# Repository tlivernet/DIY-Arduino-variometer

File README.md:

DIY Arduino variometer - with BMP085 Barometric Pressure Sensor
==================

> ### 🚧 Une refonte moderne est en cours : [`vario-esp32/`](vario-esp32/)
>
> Ce projet de 2014-2017 reste utilisable, mais il ne compile que sur l'IDE Arduino 1.5-1.6.1 et ses composants (BMP085, DS1307, Nokia 5110) ne se trouvent plus.
>
> Une refonte complète sur **ESP32-S3** est engagée dans le dossier [`vario-esp32/`](vario-esp32/) : écran Sharp Memory LCD 400×240, vario compensé en accélération par filtre de Kalman, liaison BLE vers XCTrack, PCB KiCad et boîtier imprimé en 3D, pour ~42 €. Le cœur métier y est déjà porté et couvert par 70 tests, dont un test de non-régression par bug identifié dans la version ci-dessous.
>
> Le code AVR historique de cette page n'est pas modifié.

Il s'agit de la version utilisant le capteur de pression BMP085. 
Vous trouverez une version alternative de ce code supportant le MS5611 sur la branche "[MS5611](https://github.com/sinseman/DIY-Arduino-variometer/tree/MS5611)".

- [Mise à jour](#mise-à-jour)
- [Présentation](#présentation)
- [Schéma](#schéma)
- [Installation](#installation)
- [Interface et utilisation](#interface-et-utilisation)

## MISE À JOUR

**Attention !** Lors de la dernière mise à jour le schéma de connection de l'écran a été modifié pour des soucis d'optimisations du montage.

- **PIN\_SCLK** : D8 --> D4
- **PIN\_LIGHT** : D11 --> Inchangée
- **PIN\_SCE** : D7 --> Inchangée
- **PIN\_RESET** : D6 --> D8
- **PIN\_DC** : D5 --> D6
- **PIN\_SDIN** :  D4 --> D5

Bien sûr vous pouvez adapter le code suivant l'ordre des branchements de l'écran à votre disposition.

Cela est valable aussi avec l'encodeur digital pour inverser le sens de rotation en remplaçant ```
Encoder knob(3, 2);``` par ``` Encoder knob(2, 3);```

**Il faut également ré-initialiser la mémoire EEPROM en téléversant une première fois avec la variable initialisation à true puis re-téléverser avec initialisation à false (voir partie [Installation](#installation)).**

## Présentation
### Vidéo de démo

[Participer à la discussion sur le forum parapentiste.](http://www.parapentiste.info/forum/bons-plans/variometre-maison-a-base-darduino-t33538.0.html)

### Matériel et coût

Le but de ce projet est de fabriquer un variomètre à faible coût pour une utilisation en vol libre (dans mon cas la pratique du parapente).
Voici à titre indicatif le matériel utilisé et leur prix d'achat sur eBay international (prix de janvier 2014) :

- Arduino nano V3.0	| 5,10€
- Nokia LCD 5110 | 2€
- BMP085 Digital Barometric Pressure Sensor	| 2,90€
- Digital Push Button Switch Rotary Encoder	| 4,20€
- Mini USB Battery Charging Board 5V | 0,90€
- Buzzer 8 ohm | 0,20€
- DC-DC Converter Step Up 1-5V 500mA | 1,15€
- 3,7V 600mAh LiPo Battery | 3,25€
- RTC Module for Arduino | 1,55€
- 3x 10k Ohm resistor + 1x 120 Ohm resistor | 0,10€
- Right Angle Mini Slide Switch | 0,10€	
- Cables | 3€
- Plastic Electronics Project Box Enclosure DIY 27x60x100mm | 2,40€

**TOTAL	| 26,85 €**

## Schéma

## Installation

Une fois votre montage terminé il faut compiler et téléverser le code sur votre Arduino. Pour cela il vous faudra utiliser l'IDE Arduino.

**Il faut utiliser [une version de l'IDE Arduino >= 1.5 et <= 1.6.1](https://www.arduino.cc/en/Main/OldSoftwareReleases), sinon des erreurs de compilation apparaissent !**

Tout d'abord vous devez installer les librairies fournies avec le projet. Copiez le contenu du dossier librairies dans le dossier librairies de votre installation (par exemple C:\Users\Toto\Documents\Arduino\libraries)

Ensuite éditez avec l'IDE Arduino le fichier Variometer/Variometer.ino et cliquez sur le bouton "Vérifier" en haut du logiciel. Après un certain temps le message "Compilation terminée" devrait apparaitre. Si vous avez des erreurs vérifiez que les librairies sont bien installées (cf plus haut).

Une fois la compilation OK il faut téléverser le programme sur l'Arduino à l'aide d'un câble USB par exemple et en cliquant sur le bouton "Téléverser" de l'IDE. **Mais avant cela lisez ce qui suit !**

**Lors du premier téléversement du programme sur l'Arduino il est important de mettre dans le code la variable  initialisation à true.
Celle-ci permet d'initisaliser correctement la mémoire Eeprom (stockant les statistiques et les options).**

```
bool initialisation = true; 
```

**Une fois le premier allumage fait il faut donc re-téléverser le code avec cette fois-ci initialisation à false. Si cela n’est pas fait la mémoire Eeprom sera effacée à chaque allumage !**

```
bool initialisation = false; 
```

## Interface et utilisation

Ce variomètre utilise un minimum de commande pour naviguer dans le menu et interagir avec l'interface. Nous utilisons un encodeur digital permettant trois actions: Gauche - Droite - Valider.

L'écran est celui d'un Nokia 5110, donc plutôt petit comparé aux variomètres du commerce, mais les informations essentielles y sont affichées. Ce variomètre produit des "bips" qui sont aussi bien émis lors de la navigation dans le menu que lors de l'utilisation de l'interface vario. 
Le volume est bien entendu paramétrable ainsi que la sensibilité de déclenchement en monté et en descente.

En plus de fournir des informations en temps réel, un système de détection automatique du début et de fin de vol permet d'obtenir des statistiques intéressantes.

### Menu

- Vario
- Stats
	- Retour
	- Statistiques
	- Reset
- Options
	- Retour
	- Tare
	- QNH
	- Alti
	- Montee
	- Desc
	- Light
	- Contra
	- Date

### Vario

Affichage dynamique des éléments suivants :

- Altitude (m)
- Variation d'altitude (m/s) avec jauge dynamique
- Temps de vol (heure : minute : seconde)
- Heure
- Température
- Batterie

Le réglage du volume est possible en tournant l'encodeur digital.
Lors d'un appui long sur le poussoir de l'encodeur, les statistiques sont réinitialisées.

### Stats

L'enregistrement des statistiques de vol se déclenche automatiquement.
Pour cela le variomètre détecte une prise ou une baisse d'altitude significative entrainant le statut "en vol".
Lorsqu'il n'y a pas de baisse ou de prise d'altitude significative pendant un certain temps, le statut "en vol" s'arrête.

A la fin du vol les statistiques sont sauvegardées et ne sont pas perdues à l'extinction du variomètre.

Ce programme peut enregistrer 8 rapports de vol. Une fois un vol terminé, la piste suivante d'enregistrement est sélectionnée. Si celle-ci n'est pas vide elle n'est pas écrasée. Il faut alors manuellement effacer la plage de stat en cours (avec un appui long sur le bouton depuis l'interface Vario) ou reset toutes les plages (Menu Stats --> Reset).

**Statistique**

Voici les informations statistiques disponibles :

- Date
	- Date et heure de début de vol.

- Chrono
	- Temps de vol enregistré, exprimé en heure : minute : seconde.

- AltMin
	- L'altitude minimum en mètre enregistré pendant le vol.

- AltMax
	- L'altitude maximum en mètre enregistré pendant le vol.

- Tx de chutte
	- Les taux de chute maximum et minimum en mètre par seconde enregistrés pendant le vol.

- Cumul
	- Altitude cumulée du vol (en mètre).

**Reset**

Remise à zéro des statistiques.

### Options

**Tare**

Initialise l'altitude zéro sur l'altitude actuelle.

**QNH**

Pression atmosphérique convertie au niveau de la mer selon les conditions de l'atmosphère standard.

**Alti**

Permet d'ajuster l'altitude.

**Montee**

Taux de montée déclenchant le bip.

**Desc**

Taux de descente déclenchant le bip.

**Light**

Intensité du rétro-éclairage (Off à 5)

**Contra**

Ajustement du contraste de l'écran.

**Date**

Réglage de la date et de l'heure de la pendule.

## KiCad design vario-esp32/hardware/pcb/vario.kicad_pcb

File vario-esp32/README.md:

# Variomètre ESP32-S3

Refonte complète du [variomètre DIY sur Arduino Nano](../README.md) de 2014-2017, pour du matériel sourçable en 2026 et une chaîne de développement qui fonctionne encore dans dix ans.

> **État : le coeur logiciel est terminé et testé — 166 tests.** Les pilotes matériel, le PCB et le boîtier arrivent aux étapes suivantes (voir [Feuille de route](#feuille-de-route)). **Rien de tout ceci n'a encore volé.**
>
> Documentation : `mkdocs serve` (ou voir `docs/`). Écrans rendus : `make render`.
>
> Le firmware **compile** pour l'ESP32-S3 (RAM 9,9 %, flash 12,2 %), mais aucun pilote n'a encore tourné sur du matériel.

## Pourquoi une refonte

Le montage d'origine fonctionne et il vole, mais :

- il ne compile que sur l'IDE Arduino 1.5-1.6.1, sorti en 2015 ;
- le BMP085 et le DS1307 ne se trouvent plus ;
- le vario a ~0,8 s de retard et ~0,3-0,4 m/s de bruit affiché, soit **plus que son propre seuil de déclenchement** à 0,3 m/s — d'où un bipeur qui bavarde à l'arrêt ;
- il n'a aucun test, et dix bugs identifiés dont deux graves (chrono qui ne s'arrête jamais, enregistrement qui cesse au bout de 8 vols).

## Ce qui est déjà là

Le coeur métier, en C++17 pur — aucune dépendance à Arduino, donc compilable et testable sur PC :

| Module | Rôle |
|---|---|
| `core/isa` | conversion pression → altitude (atmosphère standard), QNH borné |
| `core/vario_filter` | lissage pression + dérivée, coefficients indépendants de la cadence |
| `core/attitude` | estimation d'assiette 6 axes, **compensation centrifuge** |
| `core/kalman` | filtre à 3 états (altitude, vitesse, biais), garde de divergence |
| `core/audio_gate` | inhibition du son pendant la convergence au démarrage |
| `core/tone_law` | lois hauteur/durée des bips, profils « classique » et « moderne » |
| `core/tone_scheduler` | machine à états du bipeur : amorce continue, note, pause, hystérésis |
| `core/flight_fsm` | détection automatique décollage / atterrissage |
| `core/stats` | statistiques de vol (extrema, gain cumulé) |
| `core/flight_log` | journal en ajout seul, enregistrements de 64 octets + CRC16 |
| `core/config_schema` | table de schéma pilotant NVS, menu embarqué et IHM web |
| `core/lk8ex1` | trames LK8EX1 pour XCTrack / XCSoar |
| `core/buttons` | machine à états des trois boutons (anti-rebond, appui long, répétition) |
| `core/battery` | jauge de batterie 1S |
| `core/format` | mise en forme de la vitesse verticale |
| `ui/canvas` | tampon 1 bit, primitives, suivi des lignes modifiées |
| `ui/segment` | chiffres à sept segments, de taille libre |
| `ui/screens` | écrans vario, calibration, statistiques, menu |

**166 tests** répartis en 14 suites, dont un test de non-régression nommé pour chacun des dix bugs de la version AVR.

### Testé sans matériel

Deux techniques rendent l'essentiel vérifiable sur un PC :

- **trajectoires synthétiques** — accéléromètre, gyromètre et pression dérivés d'une même vérité terrain. Le jeu décisif est le virage coordonné établi : vitesse verticale vraie nulle mais facteur de charge de `g/cos φ`, situation où un vario naïf annonce une fausse montée de 1,5 m/s ;
- **images de référence** — les écrans sont rendus puis comparés octet par octet à des PBM versionnés.

## Installer l'environnement

```bash
./tools/doctor.sh          # ce qui manque, et pour quelle étape
./tools/setup-linux.sh     # installation guidée (--dry-run pour voir sans agir)
```

Pour seulement lancer les tests, trois paquets suffisent : `build-essential`, `git`, `python3`. Détail par usage dans [`docs/environnement.md`](docs/environnement.md).

## Compiler et tester

```bash
# Tests du coeur métier — c'est ce que vérifie la CI
make test

# Une seule suite
make test-test_kalman

# Rendre les écrans dans build/screens/*.png
make render

# Regénérer les images de référence (après un changement de mise en page ASSUMÉ)
make golden

# Firmware embarqué (nécessite PlatformIO)
pio run -e esp32s3
```

`make test` n'a besoin que de `g++` et `make` : Unity est inclus dans le dépôt (`test/support/unity`, licence MIT). `pio test -e native` fait la même chose via PlatformIO si tu préfères.

## Matériel visé

| Poste | Choix | Prix indicatif |
|---|---|---|
| MCU | ESP32-S3 (USB natif, BLE 5, 2 cœurs) | 5 € |
| Baromètre | MS5611 (derrière une interface, un BMP390 doit pouvoir le remplacer) | 4 € |
| IMU | 6 axes, pour le vario compensé en accélération | 2 € |
| Écran | Sharp Memory LCD LS027B7DH01, 400×240 | 18 € |
| Audio | piezo large bande + tampon 5 V | 1 € |
| Commande | 3 boutons étanches (gants) | 1 € |
| Horloge | DS3231SN + pile de sauvegarde | 1,5 € |
| Énergie | LiPo 1S 1500 mAh + charge USB-C | 6 € |
| Divers + PCB + PETG | | 5 € |
| **Total** | | **≈ 42 €** |

À comparer aux 26,85 € de la version 2014 (avec un écran à 2 €) et aux 250-400 € d'un vario du commerce.

Le Sharp Memory LCD a été retenu plutôt qu'un e-paper : même lisibilité en plein soleil et consommation quasi nulle à l'affichage figé, mais rafraîchissement rapide et **fonctionnement par grand froid** — un e-paper standard ralentit fortement sous 0 °C, ce qu'on rencontre couramment à 3000 m.

## Apports par rapport à la version AVR

- **Vario compensé en accélération** : fusion baro + accéléromètre par filtre de Kalman. La latence ne vient plus du filtre mais de l'intégration directe de l'accélération — d'où ~0,2 s au lieu de ~0,8 s, *et* un bruit divisé par 4 à 8 en même temps.
- **Seuil de montée utilisable à 0,2 m/s**, puisque le plancher de bruit descend sous 0,1 m/s.
- **Configuration au navigateur** par portail Wi-Fi, au lieu d'une molette et d'un écran de 84×48.
- **BLE vers XCTrack / XCSoar** (trames LK8EX1) : le vario sert aussi de capteur au téléphone.
- **Journal de vol append-only** en LittleFS, avec CRC et récupération après coupure — un vol interrompu par une batterie vide n'est plus perdu.
- **Silence au repos**, garanti par un test.

## Les dix bugs de 2017, et leur test

Chaque ligne correspond à un test de non-régression nommé dans `test/`.

| # | Bug | Test |
|---|---|---|
| 1 | Coefficients de filtre par itération, pas par Δt | `test_filter_is_sample_rate_independent` |
| 2 | `micros()` dans un `float`, comparé à travers son débordement à 71,6 min | `test_works_far_beyond_32bit_micros_wrap` |
| 3 | Aucune garde sur Δt → NaN définitif, écran et son morts | `test_zero_dt_is_rejected_without_nan` |
| 4 | Ligne de base en `int` → **le chrono ne s'arrête jamais** (~1 atterrissage sur 4) | `test_landing_detected_at_fractional_altitude` |
| 5 | État mort après 8 vols → **plus aucun enregistrement** | `test_many_consecutive_flights_are_all_detected` |
| 6 | `map()` sous-débordant → batterie à plat affichée **pleine** | `test_deeply_discharged_battery_reads_empty` |
| 7 | QNH non borné → `pow(x/0,…)` → altitude NaN définitive | `test_qnh_is_clamped` |
| 8 | Report de retenue : 1,96 m/s affiché « 1.10 » | `test_rounding_carry_does_not_produce_ten` |
| 9 | Gain cumulé intégrant le bruit, puis débordement | `test_noise_does_not_inflate_cumulative_gain` |
| 10 | Offsets EEPROM par `sizeof` de struct (diffèrent AVR/ESP32) | `test_qnh_is_clamped_by_the_schema` |

Le bipeur qui bavarde à l'arrêt, principal défaut d'usage de l'ancien vario, est verrouillé par `test_hysteresis_prevents_chatter_at_threshold`.

## Feuille de route

| Étape | Contenu | État |
|---|---|---|
| P0 | Squelette, CI, coeur métier + tests de non-régression | **fait** |
| P1 | Filtre de Kalman, assiette, inhibition du son, jeux synthétiques | **fait** |
| P2 | Couche d'affichage 400×240, 4 écrans, tests par images de référence | **fait** |
| P3 | Journal de vol, schéma de config, LK8EX1, boutons | **fait** |
| P4 | Pilotes MS5611, IMU, écran Sharp, audio LEDC ; tâches FreeRTOS | **écrit, compile** |
| P5 | Harnais de rejeu (trames brutes en USB → CSV → test) | à venir |
| P6 | Portail Wi-Fi de configuration + BLE vers XCTrack | à venir |
| P7a | Carte porteuse (modules interconnectés, ~5 $ les cinq) | câblage défini, vérifié contre le firmware |
| P7b | PCB intégré CMS + gerbers JLCPCB (pertinent vers 50 ex.) | schéma + PCB **routé** (auto) + Gerbers, relecture humaine à faire |
| P8 | Boîtier paramétrique OpenSCAD | brouillon rendu, à figer sur le PCB |

## Antériorité à consulter

- **[GNUVario-E](https://prunkdump.github.io/GNUVario-TTGO-T5-website/)** — projet français open source/open hardware très proche : ESP32, e-paper, MS5611 + MPU9250, boîtier 3D, docs FR/EN. À lire avant d'écrire du code.
- **[har-in-air/ESP8266_MPU9250_MS5611_VARIO](https://github.com/har-in-air/ESP8266_MPU9250_MS5611_VARIO)** — fusion Kalman « zéro lag », portail Wi-Fi. Source du choix MS5611 plutôt que BMP280 (pics de bruit) et du piezo large bande.
- [ESP32-Realtime-Vario](https://github.com/ghf20/ESP32-Realtime-Vario), [sensorio](https://github.com/zmolnar/sensorio), [VhARIO-ESPC3](https://github.com/har-in-air/VhARIO-ESPC3).

## Licence

À définir. Le code de 2017 n'en portait pas ; il faudra en choisir une (GPL-3.0 ou MIT) avant publication.

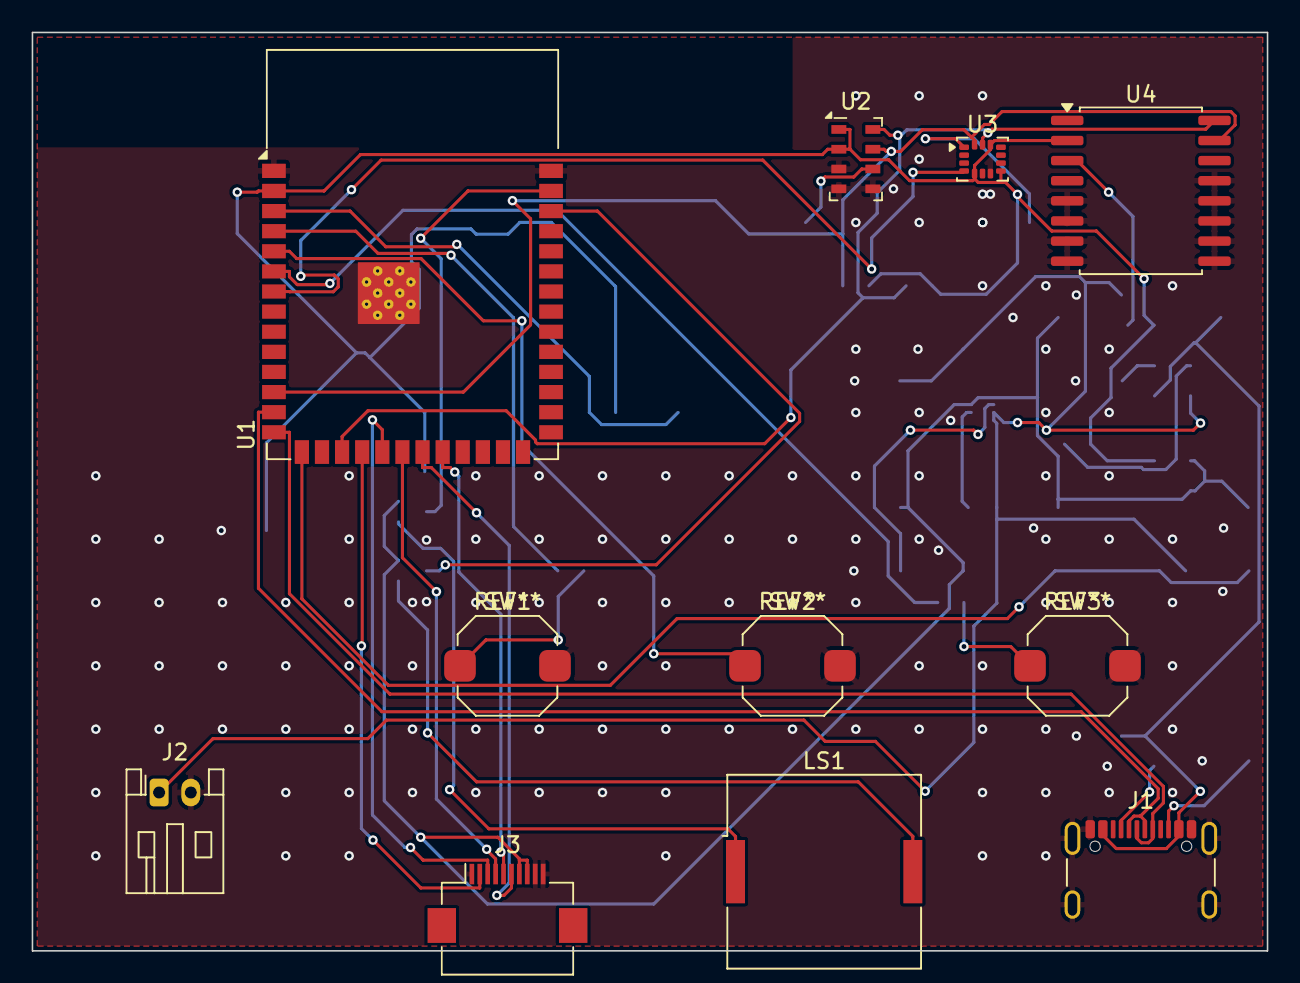
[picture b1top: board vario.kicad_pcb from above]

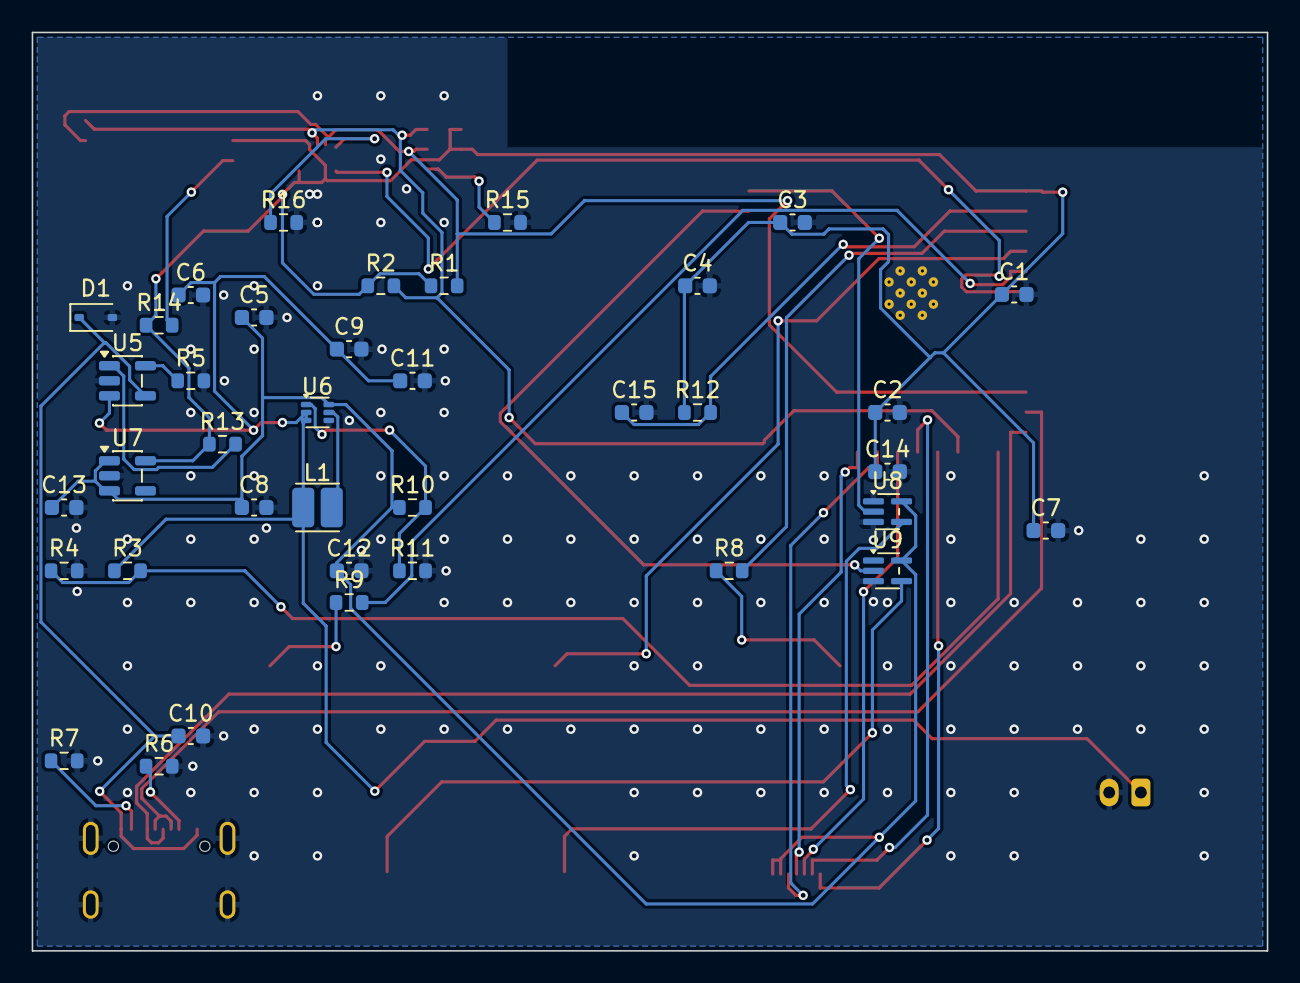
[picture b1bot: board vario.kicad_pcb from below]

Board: 2 copper layers, 78.0 x 58.0 mm, 50 parts (38 on the bottom side), 35 nets.

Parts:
BAT2: CR1220; Battery_CR1225
C1, C2, C3, C4, C5, C6: 100n; C_0603_1608Metric
C7, C8, C9, C10: 10u; C_0603_1608Metric
C11, C12: 22u; C_0603_1608Metric
C13, C14, C15: 1u; C_0603_1608Metric
D1: SMF5.0A; D_SOD-323
J1: USB4105-GF-A; USB_C_Receptacle_GCT_USB4105-xx-A_16P_TopMnt_Horizontal
J2: JST-PH-2; JST_PH_S2B-PH-K_1x02_P2.00mm_Horizontal
J3: FPC-10 LS027B7DH01; Hirose_FH12-10S-0.5SH_1x10-1MP_P0.50mm_Horizontal
L1: 2.2u; L_Cenker_CKCS252012
LS1: PIEZO 20mm; Buzzer_Murata_PKLCS1212E
R1, R2, R12, R13, R14: 10k; R_0603_1608Metric
R3, R4, R11: 100k; R_0603_1608Metric
R5: 2k; R_0603_1608Metric
R6, R7: 5.1k; R_0603_1608Metric
R8, R9: 1k; R_0603_1608Metric
R10: 910k; R_0603_1608Metric
R15, R16: 0; R_0603_1608Metric
SW1, SW2, SW3: SW_Push; SW_Push_1TS009xxxx-xxxx-xxxx_6x6x5mm
U1: ESP32-S3-WROOM-1-N16R8; ESP32-S3-WROOM-1
U2: MS5611-01BA03; LGA-8_3x5mm_P1.25mm
U3: LSM6DS3TR-C; LGA-14_3x2.5mm_P0.5mm_LayoutBorder3x4y
U4: DS3231SN; SOIC-16W_7.5x10.3mm_P1.27mm
U5: MCP73831T-2ACI/OT; SOT-23-5
U6: TPS61023DRLR; SOT-563
U7: TLV75733PDBVR; SOT-23-5
U8, U9: 74HCT1G125; SOT-353_SC-70-5

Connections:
+3V3: C1.1, C2.1, C3.1, C4.1, C7.1, C14.1, R1.1, R2.1, R12.1, R13.1, R14.1, U1.2, U2.1, U2.2, U3.5, U3.8, U3.12, U4.2, U7.5
+5V: C5.1, C8.1, C12.1, C13.1, J3.7, J3.8, R10.1, U6.6, U7.1, U7.3, U8.5, U9.5
+VBATT: C6.1, C9.1, C11.1, J2.1, L1.1, R3.1, U5.3, U6.2, U6.3
BOOST_FB: R10.2, R11.1, U6.1
BTN_DOWN: R9.1, SW3.1
BTN_DOWN_IO: R9.2, U1.6
BTN_OK: SW2.1, U1.5
BTN_UP: R8.1, SW1.1
BTN_UP_IO: R8.2, U1.4
BUZZER_A: U1.39, U8.2
BUZZER_B: U1.38, U9.2
CHG_PROG: R5.1, U5.5
CHG_STAT: R13.2, U5.1
DISP_CS: J3.2, U1.18
DISP_DISP: J3.6, U1.21
DISP_EXTCOMIN: J3.5, U1.22
DISP_MOSI: J3.3, U1.19
DISP_SCLK: J3.4, U1.20
EN: C15.1, R12.2, U1.3
GND: C1.2, C2.2, C3.2, C4.2, C5.2, C6.2, C7.2, C8.2, C9.2, C10.2, C11.2, C12.2, C13.2, C14.2, C15.2, D1.2, J1.A1, J1.A12, J1.B1, J1.B12, J1.S1, J2.2, J3.1, J3.9, J3.10, R4.2, R5.2, R6.2, R7.2, R11.2, R15.2, R16.2, SW1.2, SW2.2, SW3.2, U1.1, U1.40, U1.41, U2.3, U2.4, U2.5, U3.6, U3.7, U4.5, U4.6, U4.7, U4.8, U4.9, U4.10, U4.11, U4.12, U4.13, U5.2, U6.4, U7.2, U8.1, U8.3, U9.1, U9.3
IMU_INT1: U1.7, U3.4
IMU_SA0: R16.1, U3.1
MS_SDO: R15.1, U2.6
PIEZO_A: LS1.1, U8.4
PIEZO_B: LS1.2, U9.4
RTC_INT: R14.2, U4.3
SCL: R2.2, U1.17, U2.8, U3.13, U4.16
SDA: R1.2, U1.12, U2.7, U3.14, U4.15
SW: L1.2, U6.5
USB_CC1: J1.A5, R6.1
USB_CC2: J1.B5, R7.1
USB_D+: J1.A6, J1.B6, U1.14
USB_D-: J1.A7, J1.B7, U1.13
VBAT_SENSE: R3.2, R4.1, U1.15
VBUS: C10.1, D1.1, J1.A4, J1.A9, J1.B4, J1.B9, U5.4

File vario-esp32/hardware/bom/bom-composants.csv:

Designator,Quantity,Manufacturer,MPN,Description,Package,Fonction,Confiance MPN
U1,1,Espressif Systems,ESP32-S3-WROOM-1-N16R8,"Module Wi-Fi/BLE ESP32-S3, 16 Mo flash, 8 Mo PSRAM",Module SMD,Calculateur,haute
U2,1,TE Connectivity,MS5611-01BA03,"Capteur de pression barometrique 10-1200 mbar, resolution 10 cm",QFN-8,Barometre,haute
U3,1,STMicroelectronics,LSM6DS3TR-C,"Centrale inertielle 6 axes, accelerometre + gyrometre",LGA-14,Assiette,haute
U4,1,Analog Devices,DS3231SN#,"Horloge temps reel I2C a quartz compense en temperature, +/-2 ppm",SOIC-16,Horloge,haute
U5,1,Microchip Technology,MCP73831T-2ACI/OT,"Chargeur LiPo 1 cellule, courant reglable",SOT-23-5,Charge batterie,haute
U6,1,Texas Instruments,TPS61023DRLR,"Convertisseur elevateur 5 V, entree 0.5-5.5 V, Ilim 3.7 A",SOT-563,Rail 5 V (ecran + audio),haute
U7,1,Texas Instruments,TLV75733PDBVR,"Regulateur lineaire 3.3 V 1 A a faible chute",SOT-23-5,Rail 3.3 V,haute
U8,2,Nexperia,74HCT1G125GW,"Tampon 3 etats non inverseur, seuils TTL, alimente en 5 V, OE a la masse",SOT-353,Tampon audio push-pull,haute
DS1,1,Sharp,LS027B7DH01,"Ecran Memory LCD 2.7 pouces 400x240 reflechissant",Module + nappe FPC,Affichage,haute
J1,1,GCT,USB4105-GF-A,"Embase USB-C 16 broches, montage traversant/CMS",USB-C,Charge et liaison serie,haute
J2,1,JST,S2B-PH-K-S,"Embase 2 voies pas 2.0 mm, coudee",PH 2 voies,Batterie,haute
J3,1,Hirose,FH34SRJ-10S-0.5SH(50),"Connecteur FPC 10 voies pas 0.5 mm, ZIF",FPC-10,Nappe ecran,A VERIFIER
LS1,1,Murata,7BB-20-6L0,"Disque piezoelectrique 20 mm large bande",Disque 20 mm,Buzzer,A VERIFIER
SW1,1,Kaihong,KH-6X6X4.3H-STM,"Bouton tactile 6x6 mm CMS, hauteur 4.3 mm, 4 pattes",CMS 6x6,Bouton HAUT,haute
SW2,1,Kaihong,KH-6X6X4.3H-STM,"Bouton tactile 6x6 mm CMS, hauteur 4.3 mm, 4 pattes",CMS 6x6,Bouton VALIDER,haute
SW3,1,Kaihong,KH-6X6X4.3H-STM,"Bouton tactile 6x6 mm CMS, hauteur 4.3 mm, 4 pattes",CMS 6x6,Bouton BAS,haute
SW4,1,C&K,JS102011SAQN,"Interrupteur a glissiere SPDT",CMS,Marche/arret,haute
BAT2,1,Q&J,CR1220-2,"Support de pile CR1220 CMS (pile CR1220 3 V non fournie, a poser)",CMS,Sauvegarde horloge,haute
L1,1,Murata,DFE252012F-2R2M=P2,"Inductance de puissance 2.2 uH 3.0 A",2520 metrique,Inductance elevateur,haute
C1,6,Samsung Electro-Mechanics,CL10B104KB8NNNC,"Condensateur ceramique 100 nF 50 V X7R",0603,Decouplage,haute
C7,4,Samsung Electro-Mechanics,CL10A106MQ8NNNC,"Condensateur ceramique 10 uF 6.3 V X5R",0603,Decouplage energie,haute
C11,2,Murata,GRM188R60J226MEA0D,"Condensateur ceramique 22 uF 6.3 V X5R",0603,Filtrage elevateur,haute
C13,2,Samsung Electro-Mechanics,CL10A105KB8NNNC,"Condensateur ceramique 1 uF 50 V X5R",0603,Filtrage regulateur,haute
R1,2,Yageo,RC0603FR-0710KL,"Resistance 10 kOhm 1% 0.1 W",0603,Tirage au plus I2C,haute
R3,2,Yageo,RC0603FR-07100KL,"Resistance 100 kOhm 1% 0.1 W",0603,Diviseur mesure batterie,haute
R5,1,Yageo,RC0603FR-072KL,"Resistance 2 kOhm 1% 0.1 W",0603,Reglage courant de charge 500 mA,haute
R6,2,Yageo,RC0603FR-075K1L,"Resistance 5.1 kOhm 1% 0.1 W",0603,Tirage au moins CC1/CC2 USB-C,haute
R8,2,Yageo,RC0603FR-071KL,"Resistance 1 kOhm 1% 0.1 W",0603,Serie boutons,haute
R10,1,Uni-Royal,0603WAF9103T5E,"Resistance 910 kOhm 1% 0.1 W",0603,Contre-reaction elevateur (haut),haute
R11,1,Yageo,RC0603FR-07100KL,"Resistance 100 kOhm 1% 0.1 W",0603,Contre-reaction elevateur (bas),haute
R15,2,Yageo,RC0603FR-070RL,"Resistance 0 Ohm",0603,Selection adresse I2C baro/centrale,haute
D1,1,Littelfuse,SMF5.0A,"Diode TVS unidirectionnelle 5 V, protection ESD USB",SOD-123FL,Protection ESD VBUS,haute

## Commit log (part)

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2014-01-17 Initialisation
2014-01-17 Init
2014-01-24 Update rtc + menu + add multi stats
2014-02-11 Update Image
2014-03-27 Fix conflict
2014-04-07 Opti interface
2014-04-07 Readme
2014-04-07 Video
2014-04-07 Vidéo
2014-05-01 Optimize and update beep
2014-07-01 Markdown
2014-08-28 Update Variometer.ino
    Remplacement de :
    uint8_t percent = round((average_vcc - 3100) * 100 / (4100 - 3100));
    par :
    uint8_t percent = map(average_vcc,3100,4100,0,100);
2014-08-29 Updat stat trigger
2014-08-29 Fixed a bug on the stat trigger.
2014-08-30 Optimizations
2014-08-31 Update librairies
2014-09-09 ConfirmMelody lors du changement de volume.
    Rajout d'un son lors du changement du volume. Permet d'aprécier le changement du volume.
2015-02-03 Improved beeps and schema
2015-02-06 Improved beeps
2015-02-11 Update librairies + optimizations
    loop time and memory optimization
2015-02-11 Optimize display
2015-02-12 More rendering optimizations
2015-02-17 Shematic + readme fixes
2015-02-19 Others memory optimizations
2015-02-20 More memory optimizations
2015-02-21 more & more memory optimizations
2015-03-02 Add QNH option
2015-03-16 Optimizations
    improve stats rendering and cumulative altitude
2015-03-16 Improve stat trigger
    improvement of the detection of the altitude to trigger stopping
    statistics
2015-05-04 Add parapentiste forum link
2016-03-15 MS5611 support
2016-03-15 README Update
2017-09-19 Update battery levels
    Issue #4 : mise à jour des tensions de batterie pour les li-ion / li-po actuelles
    + de durée de vie (cycles)
    + de sécu
